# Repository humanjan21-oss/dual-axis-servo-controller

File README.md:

# Dual-Axis Servo Controller

A dual-axis positioning controller built around the PIC18F26K80, using continuous-rotation servos, quadrature encoder feedback, and RS485 communication.

## Why this project exists

This project started as a practical way for my son and me to explore electronics, mechanics, and programming together.

The aim is to build a reusable controller while learning about motion control, position feedback, and communication between devices. Possible applications include robotic arms, steering mechanisms, and other experimental motion projects.

## Main hardware

- PIC18F26K80 microcontroller
- Two modified MG996R continuous-rotation servos
- Two quadrature encoders for position feedback
- MAX485E RS485 interface
- ACS712 current sensing
- External 12 V to 6 V power supply stage

## Current status

The design is under development. Hardware testing and performance validation are pending.

Files and documentation will be added as the project progresses. Published designs may change following testing.

## Hardware files

- `Servo PID Controller/` — Editable KiCad project, schematic, and PCB layout.
- `Servo PID Controller/Production Export/` — PCB manufacturing files, including the Gerber ZIP prepared for JLCPCB.

To inspect or modify the design, download the repository and open the project in KiCad.

The Gerber ZIP can be uploaded directly to JLCPCB for a manufacturing preview. Check the board dimensions, layer count, and manufacturing settings against the KiCad design before ordering.

## Development status

The hardware design is shared for learning and development. Hardware testing and performance validation are pending, so the PCB should be treated as an unverified prototype.

Firmware and test results will be added as development progresses.

## Intended operation

A master device sends position targets over RS485. The controller uses encoder feedback to move each axis towards its target and report its status.

Standalone, PC, and wireless control options are areas for future development.

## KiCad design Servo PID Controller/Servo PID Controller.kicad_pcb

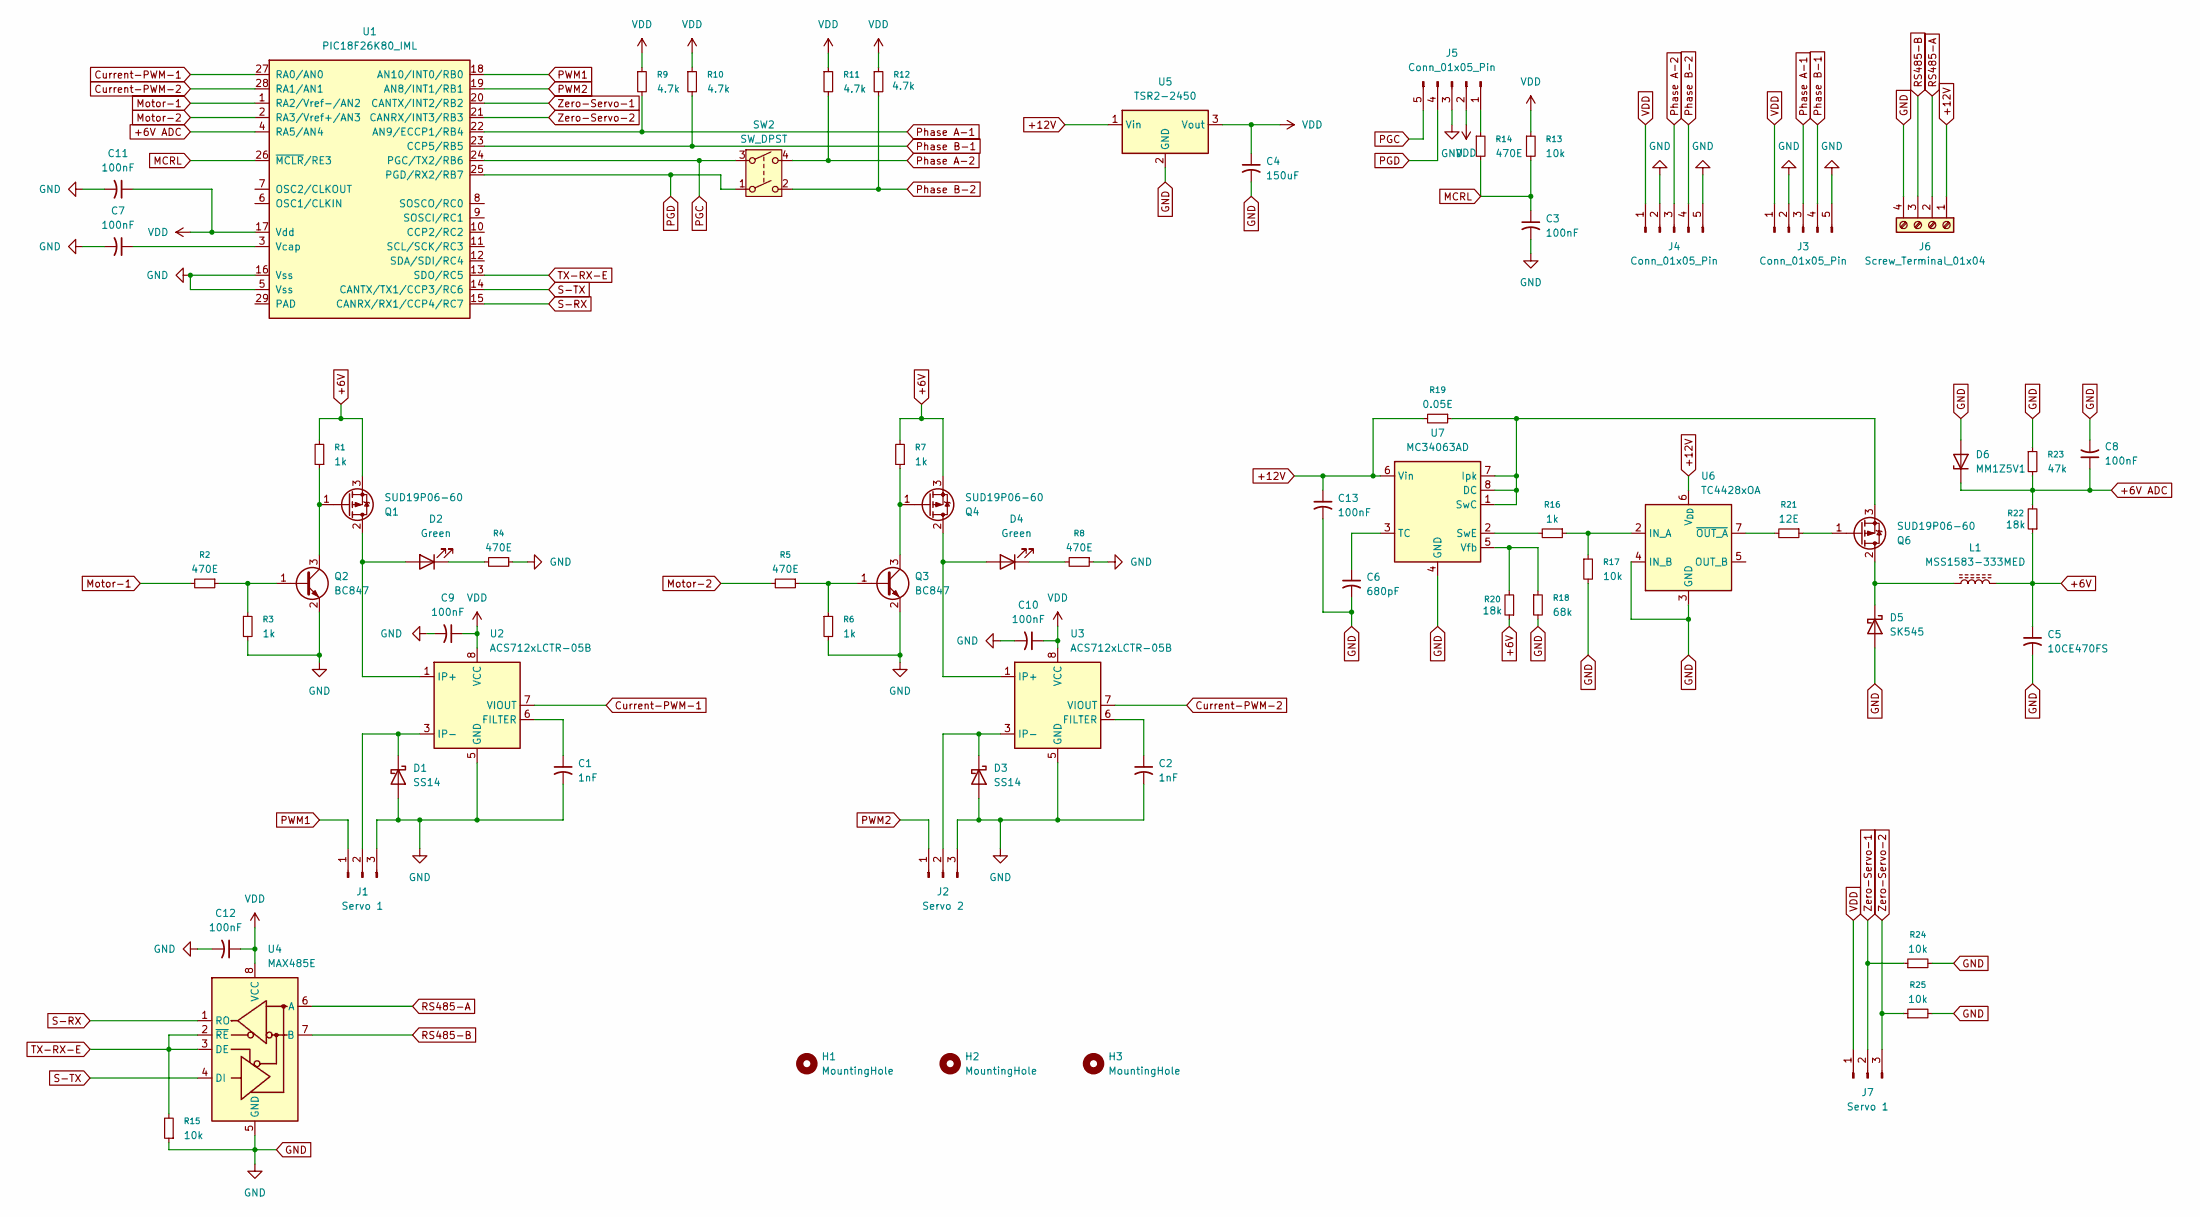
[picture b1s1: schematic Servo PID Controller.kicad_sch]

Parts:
C1, C2: 1nF; C_1206_3216Metric_Pad1.33x1.80mm_HandSolder
C3, C7, C8, C9, C10, C11, C12, C13: 100nF; C_1206_3216Metric_Pad1.33x1.80mm_HandSolder
C4: 150uF; C_Elec_6.3x5.8
C5: 10CE470FS; C_Elec_8x10.2
C6: 680pF; C_1206_3216Metric_Pad1.33x1.80mm_HandSolder
D1, D3: SS14; D_SMA
D2, D4: Green; LED_1206_3216Metric_Pad1.42x1.75mm_HandSolder
D5: SK545; D_SMC_Handsoldering
D6: MM1Z5V1; D_SOD-123
H1, H2, H3: MountingHole; MountingHole_3.2mm_M3
J1, J7: Servo 1; Harwin_M20-89003xx_1x03_P2.54mm_Horizontal
J2: Servo 2; Harwin_M20-89003xx_1x03_P2.54mm_Horizontal
J3, J4, J5: Conn_01x05_Pin; Harwin_M20-89005xx_1x05_P2.54mm_Horizontal
J6: Screw_Terminal_01x04; TerminalBlock_MetzConnect_Type101_RT01604HBWC_1x04_P5.08mm_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
L1: MSS1583-333MED; L_Coilcraft_MSS1583-XXX
Q1, Q4, Q6: SUD19P06-60; TO-252-2
Q2, Q3: BC847; SOT-23
R1, R3, R6, R7, R16: 1k; R_1206_3216Metric_Pad1.30x1.75mm_HandSolder
R2, R4, R5, R8, R14: 470E; R_1206_3216Metric_Pad1.30x1.75mm_HandSolder
R9, R10, R11, R12: 4.7k; R_1206_3216Metric_Pad1.30x1.75mm_HandSolder
R13, R15, R17, R24, R25: 10k; R_1206_3216Metric_Pad1.30x1.75mm_HandSolder
R18: 68k; R_1206_3216Metric_Pad1.30x1.75mm_HandSolder
R19: 0.05E; R_2512_6332Metric_Pad1.40x3.35mm_HandSolder
R20, R22: 18k; R_1206_3216Metric_Pad1.30x1.75mm_HandSolder
R21: 12E; R_2512_6332Metric_Pad1.40x3.35mm_HandSolder
R23: 47k; R_1206_3216Metric_Pad1.30x1.75mm_HandSolder
SW2: SW_DPST; SW_DIP_SPSTx02_Slide_6.7x6.64mm_W8.61mm_P2.54mm_LowProfile
U1: PIC18F26K80_IML; QFN-28-1EP_6x6mm_P0.65mm_EP4.25x4.25mm
U2, U3: ACS712xLCTR-05B; SOIC-8_3.9x4.9mm_P1.27mm
U4: MAX485E; SOIC-8_3.9x4.9mm_P1.27mm
U5: TSR2-2450; Converter_DCDC_TRACO_TSR2-xxxx_THT
U6: TC4428xOA; SOIC-8_3.9x4.9mm_P1.27mm
U7: MC34063AD; SOIC-8_3.9x4.9mm_P1.27mm

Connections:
+6V: C5.1, L1.2, Q1.3 (S), Q4.3 (S), R1.2, R7.2, R20.1, R22.1
+6V ADC: C8.1, D6.1 (K), R22.2, R23.2, U1.4 (RA5/AN4)
+12V: C13.1, J6.1, R19.2, U5.1 (Vin), U6.6 (V_{DD}), U7.6 (Vin)
Current-PWM-1: U1.27 (RA0/AN0), U2.7 (VIOUT)
Current-PWM-2: U1.28 (RA1/AN1), U3.7 (VIOUT)
GND: C1.2, C2.2, C3.2, C4.2, C5.2, C6.2, C7.2, C8.2, C9.2, C10.2, C11.2, C12.2, C13.2, D1.2 (A), D3.2 (A), D5.2 (A), D6.2 (A), J1.3, J2.3, J3.2, J3.5, J4.2, J4.5, J5.3, J6.4, Q2.2 (E), Q3.2 (E), R3.2, R4.1, R6.2, R8.1, R15.1, R17.2, R18.2, R23.1, R24.2, R25.2, U1.5 (Vss), U1.16 (Vss), U2.5 (GND), U3.5 (GND), U4.5 (GND), U5.2 (GND), U6.3 (GND), U6.4 (IN_B), U7.4 (GND)
MCRL: C3.1, R13.2, R14.2, U1.26 (~MCLR/RE3)
Motor-1: R2.2, U1.1 (RA2/Vref-/AN2)
Motor-2: R5.2, U1.2 (RA3/Vref+/AN3)
unnamed: D1.1 (K), J1.2, U2.3 (IP-), U2.4 (IP-)
unnamed: D2.2 (A), Q1.2 (D), U2.1 (IP+), U2.2 (IP+)
unnamed: D2.1 (K), R4.2
unnamed: D3.1 (K), J2.2, U3.3 (IP-), U3.4 (IP-)
unnamed: D4.2 (A), Q4.2 (D), U3.1 (IP+), U3.2 (IP+)
unnamed: D4.1 (K), R8.2
unnamed: D5.1 (K), L1.1, Q6.2 (D)
unnamed: J5.1, R14.1
unnamed: Q1.1 (G), Q2.3 (C), R1.1
unnamed: Q2.1 (B), R2.1, R3.1
unnamed: Q3.1 (B), R5.1, R6.1
unnamed: Q3.3 (C), Q4.1 (G), R7.1
unnamed: Q6.1 (G), R21.1
unnamed: Q6.3 (S), R19.1, U7.1 (SwC), U7.7 (Ipk), U7.8 (DC)
unnamed: C7.1, U1.3 (Vcap)
unnamed: C1.1, U2.6 (FILTER)
unnamed: C2.1, U3.6 (FILTER)
unnamed: R16.1, R17.1, U6.2 (IN_A)
unnamed: R21.2, U6.7 (~OUT_A)
unnamed: R16.2, U7.2 (SwE)
unnamed: C6.1, U7.3 (TC)
unnamed: R18.1, R20.2, U7.5 (Vfb)
PGC: J5.5, SW2.3, U1.24 (PGC/TX2/RB6)
PGD: J5.4, SW2.1, U1.25 (PGD/RX2/RB7)
PWM1: J1.1, U1.18 (AN10/INT0/RB0)
PWM2: J2.1, U1.19 (AN8/INT1/RB1)
Phase A-1: J3.3, R9.2, U1.22 (AN9/ECCP1/RB4)
Phase A-2: J4.3, R11.2, SW2.4
Phase B-1: J3.4, R10.2, U1.23 (CCP5/RB5)
Phase B-2: J4.4, R12.2, SW2.2
RS485-A: J6.2, U4.6 (A)
RS485-B: J6.3, U4.7 (B)
S-RX: U1.15 (CANRX/RX1/CCP4/RC7), U4.1 (RO)
S-TX: U1.14 (CANTX/TX1/CCP3/RC6), U4.4 (DI)
TX-RX-E: R15.2, U1.13 (SDO/RC5), U4.2 (~RE), U4.3 (DE)
VDD: C4.1, C9.1, C10.1, C11.1, C12.1, J3.1, J4.1, J5.2, J7.1, R9.1, R10.1, R11.1, R12.1, R13.1, U1.17 (Vdd), U2.8 (VCC), U3.8 (VCC), U4.8 (VCC), U5.3 (Vout)
Zero-Servo-1: J7.2, R24.1, U1.20 (CANTX/INT2/RB2)
Zero-Servo-2: J7.3, R25.1, U1.21 (CANRX/INT3/RB3)

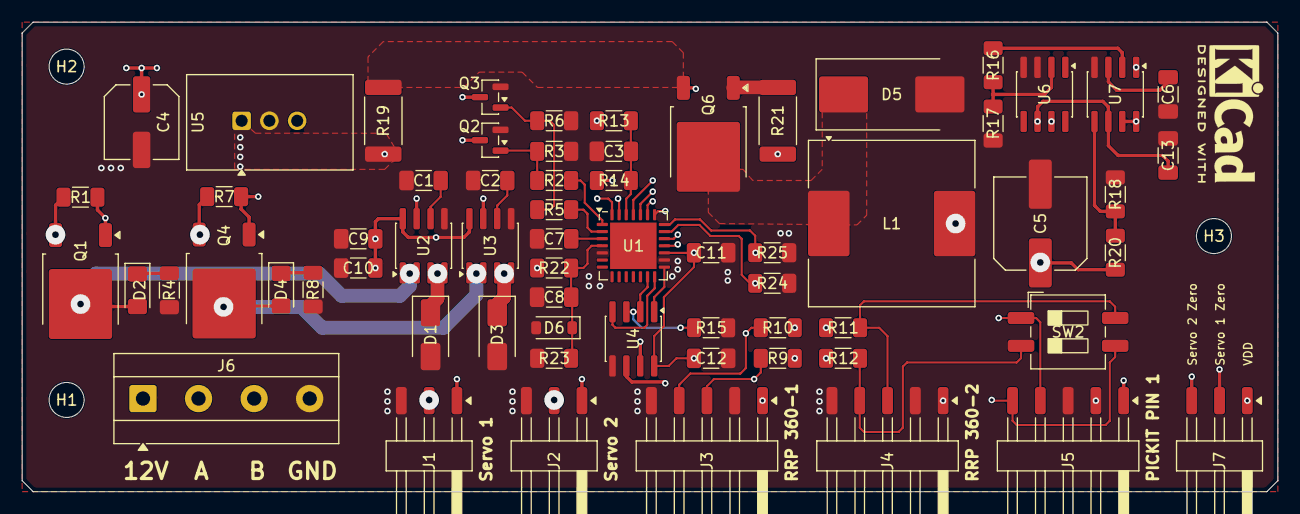
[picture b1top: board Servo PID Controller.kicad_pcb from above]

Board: 4 copper layers, 114.8 x 42.9 mm, 68 parts (0 on the bottom side), 47 nets.
